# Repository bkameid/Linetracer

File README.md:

Este repositorio corresponde al proyectro de robot velocista linetracer del Grupo 10 de la 12a sección de módulo interdisciplinario de la universidad de Chile en 2025.

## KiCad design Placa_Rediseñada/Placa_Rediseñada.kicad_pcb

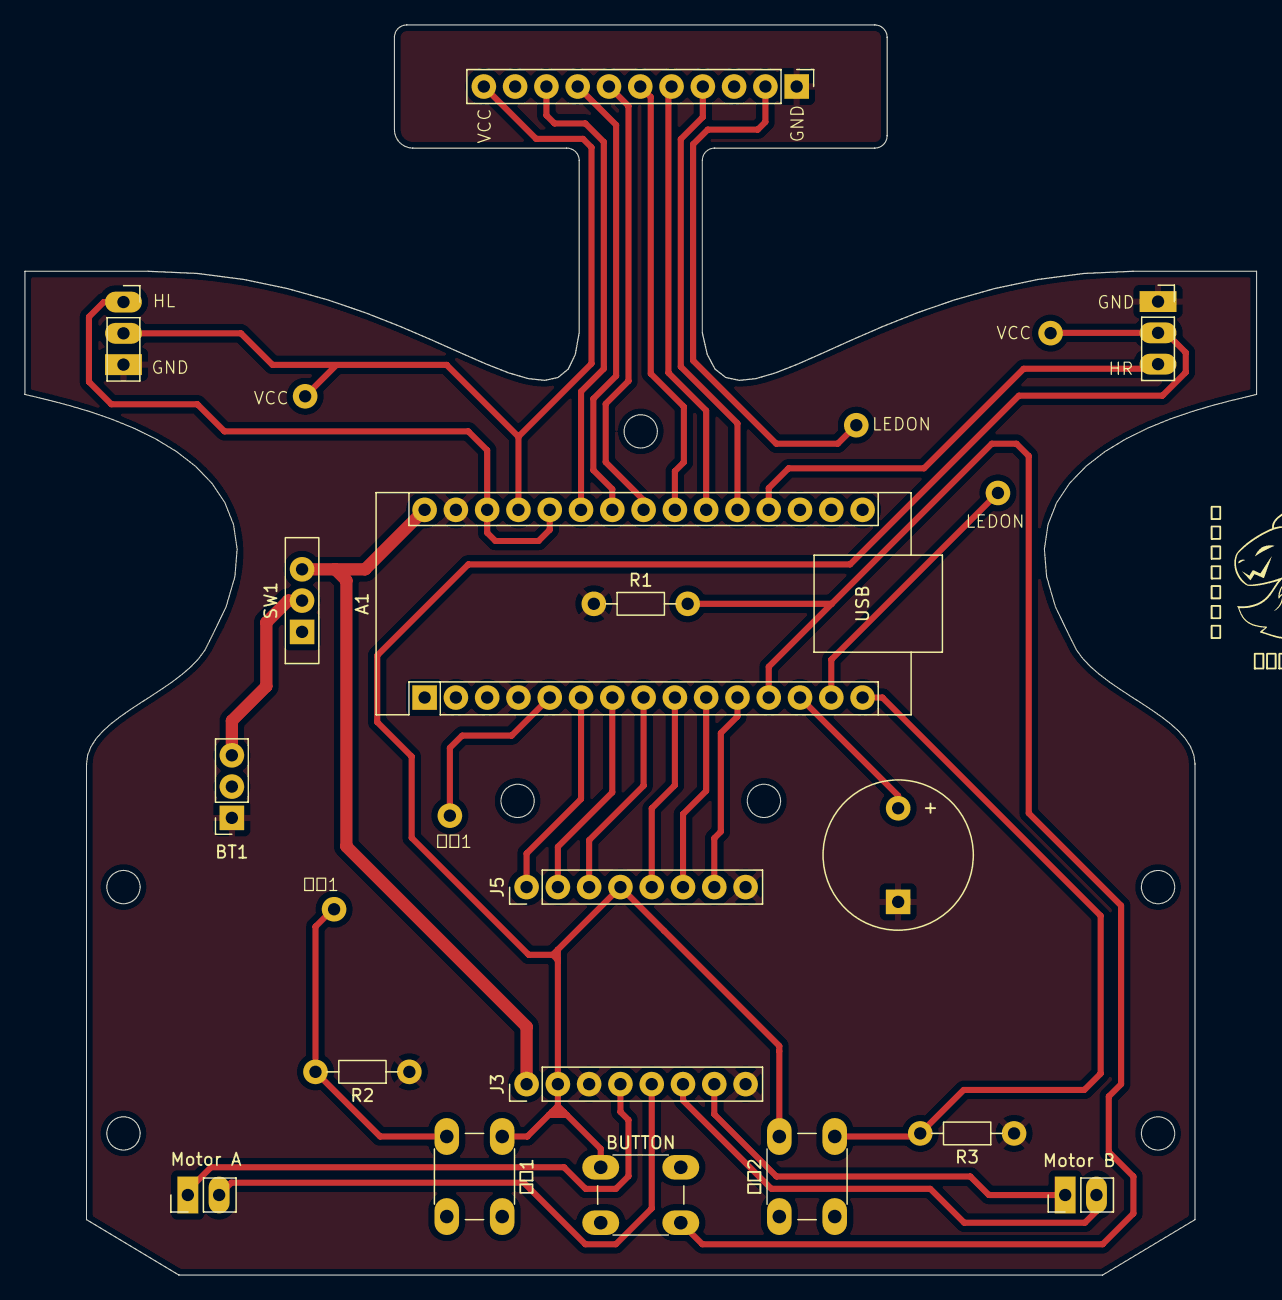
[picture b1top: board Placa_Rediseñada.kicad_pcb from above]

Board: 2 copper layers, 100.0 x 101.4 mm, 17 parts (0 on the bottom side), 27 nets.

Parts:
A1: Arduino_Nano_Every; Arduino_Nano
BT1: Battery; PinSocket_1x03_P2.54mm_Vertical
BUTTON: SW_Push; SW_PUSH_6mm_H5mm
BZ1: Buzzer; Buzzer_12x9.5RM7.6
GND: LineSensor; PinHeader_1x11_P2.54mm_Vertical
HL: Conn_01x03_MountingPin; PinSocket_1x03_P2.54mm_Vertical
HR1: Conn_01x03_MountingPin; PinSocket_1x03_P2.54mm_Vertical
J3, J5: Conn_01x08; PinHeader_1x08_P2.54mm_Vertical
Motor A: Motor_DC; PinHeader_1x02_P2.54mm_Vertical
Motor B: Motor_DC; PinHeader_1x02_P2.54mm_Vertical
R1: 47KΩ; R_Axial_DIN0204_L3.6mm_D1.6mm_P7.62mm_Horizontal
R2, R3: 10KΩ; R_Axial_DIN0204_L3.6mm_D1.6mm_P7.62mm_Horizontal
SW1: SW_Nidec_CAS-120A1; SW_Slide-03_Wuerth-WS-SLTV_10x2.5x6.4_P2.54mm
电钮1, 电钮2: SW_Push; SW_PUSH_6mm_H5mm

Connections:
7.4V: A1.30 (VIN), J3.1, SW1.3 (A)
A01: J3.4, Motor A.1 (+)
A02: J3.5, Motor A.2 (-)
AIN1: A1.7 (D4), J5.2
AIN2: A1.8 (D5), J5.3
B01: J3.7, Motor B.1 (+)
B02: J3.6, Motor B.2 (-)
BIN1: A1.9 (D6), J5.5
BIN2: A1.10 (D7), J5.6
BUTTON: A1.12 (D9), BUTTON.2, R1.2
BUZZER: A1.13 (D10), BZ1.1 (+)
D1: A1.20 (A1), GND.4
D2: A1.21 (A2), GND.5
D3: A1.22 (A3), GND.6
D4: A1.23 (SDA/A4), GND.7
D5: A1.24 (SCL/A5), GND.8
D6: A1.25 (A6), GND.9
GND: A1.4 (GND), A1.29 (GND), BT1.2 (-), BZ1.2 (-), GND.1, HL.3, HR1.3, J3.3, J3.8, J5.8, R1.1, R2.1, R3.1
HL: A1.26 (A7), A1.28 (~RESET), HL.1
HR: A1.19 (A0), HR1.1
LEDON: A1.14 (MOSI), GND.2
unnamed: BT1.1 (+), SW1.2 (B)
PWMA: A1.6 (D3), J5.1
PWMB: A1.11 (D8), J5.7
VCC: A1.27 (+5V), BUTTON.1, GND.11, HL.2, HR1.2, J3.2, J5.4, 电钮1.1, 电钮2.1
电钮1: A1.5 (D2), R2.2, 电钮1.2
电钮2: A1.15 (MISO), R3.2, 电钮2.2

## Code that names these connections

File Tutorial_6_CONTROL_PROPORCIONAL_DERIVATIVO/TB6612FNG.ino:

# define AIN1 8    // pin 1 de dirección del Motor Izquierdo
# define AIN2 9    // pin 2 de dirección del Motor Izquierdo
# define PWMA 5    // pin PWM del Motor Izquierdo


# define BIN1 4    // pin 1 de dirección del Motor Derecho
# define BIN2 7    // pin 2 de dirección del Motor Derecho
# define PWMB 6    // pin PWM del Motor Derecho


void TB6612FNG_init() {
    pinMode(AIN1, OUTPUT);
    pinMode(AIN2, OUTPUT);
    pinMode(PWMA, OUTPUT);
    pinMode(BIN1, OUTPUT);
    pinMode(BIN2, OUTPUT);
    pinMode(PWMB, OUTPUT);
}

void MotorIz(int value) {
    if (value >= 0) {
        // si valor positivo vamos hacia adelante

        digitalWrite(AIN1, HIGH);
        digitalWrite(AIN2, LOW);
    } else {
        // si valor negativo vamos hacia atras

        digitalWrite(AIN1, LOW);
        digitalWrite(AIN2, HIGH);
        value *= -1;
    }

    // Setea Velocidad
    analogWrite(PWMA, value);
}


void MotorDe(int value) {
    if (value >= 0) {
        // si valor positivo vamos hacia adelante

        digitalWrite(BIN1, HIGH);
        digitalWrite(BIN2, LOW);
    } else {
        // si valor negativo vamos hacia atras

        digitalWrite(BIN1, LOW);
        digitalWrite(BIN2, HIGH);
        value *= -1;
    }

    // Setea Velocidad

    analogWrite(PWMB, value);
}


void Motores(int left, int right) {
    MotorIz(left);
    MotorDe(right);
}

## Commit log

2025-09-10 Carpeta de motor añadida
2025-09-22 Nombres de sketches y carpetas sincronizados
2025-10-01 Sigue-Linea
    Primer intento de que el robot siga una linea con PID
2025-10-09 Summary(required)
2025-10-15 Updating situation
2025-10-20 misc
2025-11-04 Tutorial 6 added
2025-11-19 Change name
